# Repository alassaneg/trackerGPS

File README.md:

# trackerGPS
Tracker GPS with gsm functionality and eSim.
Kicad files in the folder "/trackerGPS"

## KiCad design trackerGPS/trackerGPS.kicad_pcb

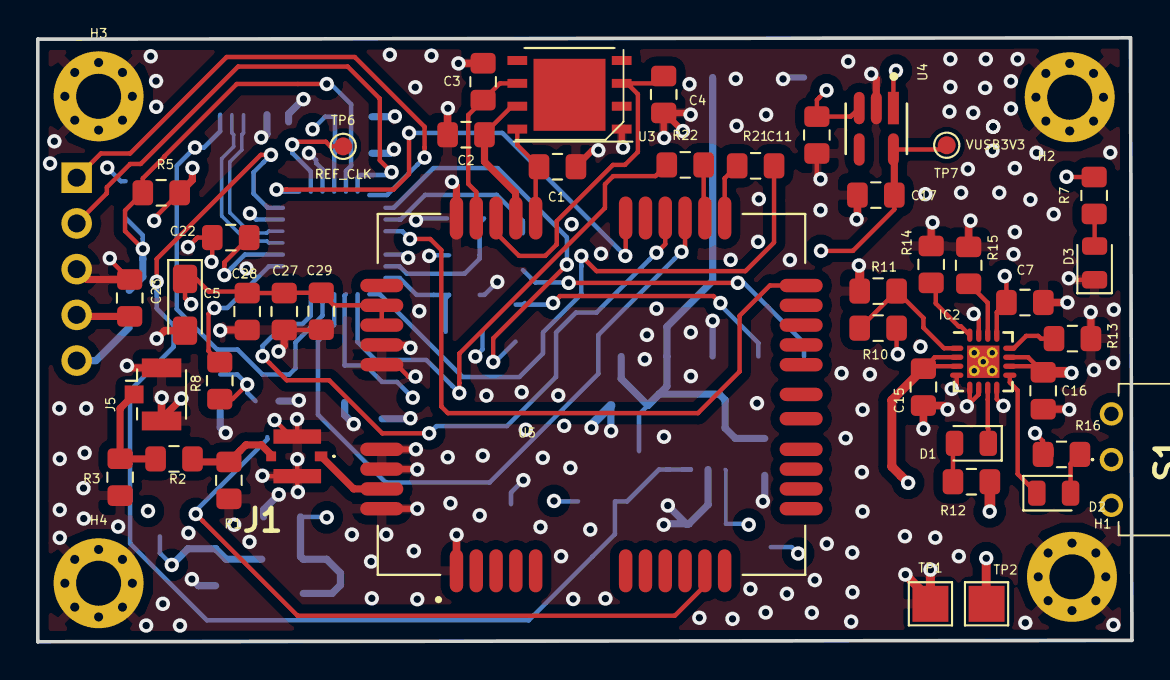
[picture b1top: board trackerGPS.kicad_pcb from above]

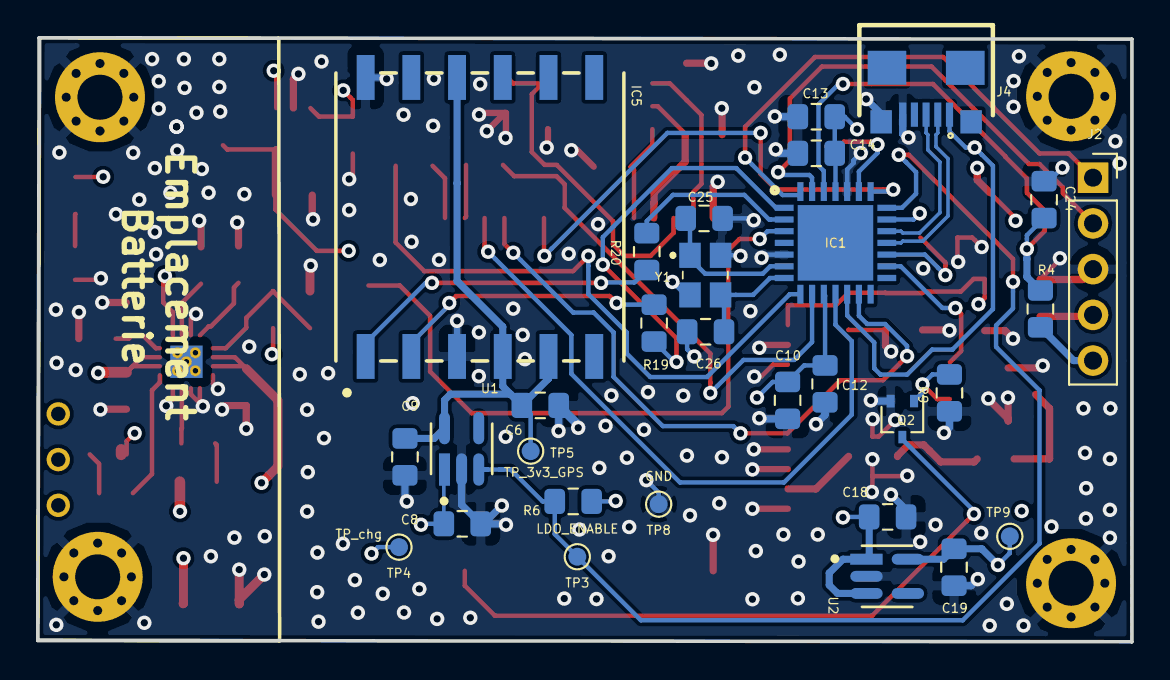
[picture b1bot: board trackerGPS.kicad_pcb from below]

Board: 4 copper layers, 60.8 x 33.6 mm, 78 parts (30 on the bottom side), 50 nets.

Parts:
C1, C7: 1uF; C_0805_2012Metric_Pad1.15x1.40mm_HandSolder
C2, C3, C4, C27: 33pF; C_0805_2012Metric_Pad1.15x1.40mm_HandSolder
C5: 100uF; CP_EIA-3216-10_Kemet-I_Pad1.58x1.35mm_HandSolder
C6, C22: 10uF; C_0805_2012Metric_Pad1.15x1.40mm_HandSolder
C8, C9, C15, C16, C18, C19: 4.7uF; C_0805_2012Metric_Pad1.15x1.40mm_HandSolder
C10, C11, C13, C17, C23, C24, C28: 100nF; C_0805_2012Metric_Pad1.15x1.40mm_HandSolder
C12, C14: 1nF; C_0805_2012Metric_Pad1.15x1.40mm_HandSolder
C25, C26: 28pF; C_0805_2012Metric_Pad1.15x1.40mm_HandSolder
C29: 10pF; C_0805_2012Metric_Pad1.15x1.40mm_HandSolder
D1, D2, D3: LED_Small; LED_0805_2012Metric
H1, H2, H3, H4: MountingHole_Pad; MountingHole_2.5mm_Pad_Via
IC1: PIC32MM0256GPM028-I_ML; QFN65P600X600X100-29N-D
IC2: BQ24072TRGTT; QFN-16-1EP_3x3mm_P0.5mm_EP2.7x2.7mm_ThermalVias
IC5: L86-M33; L80-M39
J1: MS-156HF; MS156HF
J2: Conn; PinSocket_1x05_P2.54mm_Vertical
J4: USB_B_Micro; DX4R005HJ5
J5: Conn_Coaxial; U.FL_Hirose_U.FL-R-SMT-1_Vertical
Q2: BC847BW,115; SOT-323_SC-70
R1, R3: R_Small; R_0805_2012Metric_Pad1.15x1.40mm_HandSolder
R2, R6, R15, R19, R20, R21, R22: 0ohm; R_0805_2012Metric_Pad1.15x1.40mm_HandSolder
R4: 602ohm; R_0805_2012Metric_Pad1.15x1.40mm_HandSolder
R5, R8: 10kOhm; R_0805_2012Metric_Pad1.15x1.40mm_HandSolder
R7: 1.9kOhm; R_0805_2012Metric_Pad1.15x1.40mm_HandSolder
R9: 47kOhm; R_0805_2012Metric_Pad1.15x1.40mm_HandSolder
R10: 200kOhm; R_0805_2012Metric_Pad1.15x1.40mm_HandSolder
R11: 49.9kOhm; R_0805_2012Metric_Pad1.15x1.40mm_HandSolder
R12, R16: 1.5kOhm; R_0805_2012Metric_Pad1.15x1.40mm_HandSolder
R13: NP; R_0805_2012Metric_Pad1.15x1.40mm_HandSolder
R14: 909 ohm; R_0805_2012Metric_Pad1.15x1.40mm_HandSolder
S1: 450302014072
TP1: Battery_GND; TestPoint_Pad_2.0x2.0mm
TP2: Battery+; TestPoint_Pad_2.0x2.0mm
TP3: LDO_ENABLE; TestPoint_Pad_D1.0mm
TP4: TP_chg; TestPoint_Pad_D1.0mm
TP5: TP_3v3_GPS; TestPoint_Pad_D1.0mm
TP6: REF_CLK; TestPoint_Pad_D1.0mm
TP7: VUSB3V3; TestPoint_Pad_D1.0mm
TP8: GND; TestPoint_Pad_D1.0mm
TP9: TP_3v3_UC; TestPoint_Pad_D1.0mm
U1, U2, U4: REG113NA-3.3_3K; Texas_Instruments-DBV0005A-0-0-IPC_A
U3: MFF2_E_SIM; DFN-8-1EP_6x5mm_P1.27mm_EP4x4mm
U5: M95; XCVR_M95
Y1: ABM8G-48.000MHZ-18-D2Y-T; ABM8G48000MHZ18D2YT

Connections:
/gpsModule/UART_RX_GSM: IC5.1, R20.2
/gpsModule/UART_TX_GSM: IC5.2, R19.1
/microcontroller/CALL_RECEIVED: IC1.22, U5.26
/microcontroller/LDO_ENABLE: IC1.21, R6.1, TP3.1, U1.3
/microcontroller/SLEEP: IC1.3, U5.20
/microcontroller/UART_CTS3_UC: IC1.11, U5.23
/microcontroller/UART_RX2_UC: IC1.1, R19.2
/microcontroller/UART_RX3_UC: IC1.9, R22.1
/microcontroller/UART_TX2_UC: IC1.2, R20.1
/microcontroller/UART_TX3_UC: IC1.8, R21.2
/microcontroller/USB+: IC1.19, J4.3
/microcontroller/USB-: IC1.18, J4.2
/microcontroller/VBUS: C7.1, C11.1, IC1.12, IC2.13, J4.1, R10.2, U4.1, U4.3
/microcontroller/VUSB3V3: C17.1, IC1.20, TP7.1, U4.5
/powerSupply/Vcc_3.3V_GPS: C6.1, C9.1, IC5.4, IC5.5, IC5.10, TP5.1, U1.5
/powerSupply/Vcc_3.3V_UC: C10.1, C12.1, C13.1, C14.1, C19.1, C23.1, IC1.10, IC1.25, J2.4, R5.2, TP9.1, U2.5
/powerSupply/Vcc_BAT_GSM: C5.1, C8.1, C16.1, C18.1, C27.1, C28.1, C29.1, IC2.10, IC2.11, R6.2, R7.2, R12.2, R16.2, TP4.1, U1.1, U2.1, U2.3, U5.33, U5.34
/simModule/GSM_POWER_ON: Q2.3, U5.10
/simModule/UART_GSM_RTS: IC1.13, U5.24
/simModule/UART_RX_GSM: R21.1, U5.21
/simModule/UART_TX_GSM: R22.2, U5.22
GND: C1.2, C2.2, C3.2, C4.2, C5.2, C6.2, C7.2, C8.2, C9.2, C10.2, C11.2, C12.2, C13.2, C14.2, C15.2, C16.2, C17.2, C18.2, C19.2, C22.2, C23.2, C24.2, C25.2, C26.2, C27.2, C28.2, C29.2, D3.1, H1.1, H2.1, H3.1, H4.1, IC1.5, IC1.24, IC2.4, IC2.5, IC2.6, IC2.8, IC2.15, IC2.17, IC5.3, IC5.12, J1.MP1, J1.MP2, J2.3, J4.5, J4.6, J5.2, Q2.2, R1.1, R3.2, R9.2, R11.1, R13.1, R14.1, R15.1, TP1.1, TP8.1, U1.2, U2.2, U3.1, U4.2, U5.1, U5.31, U5.35, U5.36, U5.37, U5.38, U5.40, Y1.2, Y1.4
unnamed: C1.1, U3.8, U5.27
unnamed: C2.1, U3.7, U5.28
unnamed: C3.1, U3.6, U5.30
unnamed: C4.1, U3.3, U5.29
unnamed: C15.1, IC2.2, IC2.3, S1.2
unnamed: C22.1, IC1.17
unnamed: C24.1, IC1.26, R4.1, R5.1
unnamed: C25.1, IC1.6, Y1.1
unnamed: C26.1, IC1.7, Y1.3
unnamed: D1.1, IC2.7
unnamed: D1.2, R12.1
unnamed: D2.1, IC2.9
unnamed: D2.2, R16.1
unnamed: D3.2, R7.1
unnamed: IC1.16, R8.2
unnamed: IC1.23, TP6.1
unnamed: IC1.27, J2.2
unnamed: IC1.28, J2.1
unnamed: IC2.1, R10.1, R11.2
unnamed: IC2.12, R13.2
unnamed: IC2.14, R15.2
unnamed: IC2.16, R14.2
unnamed: J1.A1, U5.39
unnamed: J1.C1, R1.2, R2.1
unnamed: J2.5, R4.2
unnamed: J5.1, R2.2, R3.1
unnamed: Q2.1, R8.1, R9.1
unnamed: S1.1, TP2.1

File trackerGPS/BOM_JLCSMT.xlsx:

Comment | Designator | Footprint | LCSC Part #（optional）
1uF | C1, C7 | 0805_C | C28323
33pF | C2 , C3, C4, C27 | 0805_C | C1814
100uF | C5 | CP_EIA-3216-10_Kemet-I_Pad1.58x1.35mm_HandSolder | C313517
10uF | C6, C22 | 0805_C | C282736
4.7uF | C8, C9, C15, C16, C18, C19 | 0805_C | C354262
1nF | C12, C14 | 0805_C | C501242
28pF | C25, C26 | 0805_C
100nF | C10, C11, C13, C17, C23, C24, C28 | 0805_C | C167411
10pF | C29 | 0805_C | C157608
LED_Small | D1, D2, D3 | 0805_L | C188728
PIC32MM0256GPM028-I_ML | IC1 | QFN65P600X600X100-29N-D
BQ24072TRGTT | IC2 | QFN-16-1EP_3x3mm_P0.5mm_EP2.7x2.7mm_ThermalVias
L86-M33 | IC5 | L86-M33
Conn | J2 | PinSocket_1x05_P2.54mm_Vertical
902-9235 | J3 | 902-9235
USB_B_Micro | J4 | DX4R005HJ5
Conn_Coaxial | J1 | U.FL_Hirose_U.FL-R-SMT-1_Vertical
BC847BW,115 | Q2 | SOT-323_SC-70 | C8659
R_Small | R1 | 0805_R
R_Small | R3 | 0805_R
602ohm | R4 | 0805_R | C17777
10kOhm | R5, R8 | 0805_R | C17414
1.9kOhm | R7 | 0805_R
47kOhm | R9 | 0805_R | C17713
200kOhm | R10 | 0805_R | C17539
49.9kOhm | R11 | 0805_R | C63044
NP | R13 | 0805_R
909 ohm | R14 | 0805_R | C17863
1.5kOhm | R12, R16 | 0805_R | C4310
0ohm | R2, R6, R15, R19, R20, R21, R22 | 0805_R | C17477
REG113NA-3.3_3K | U1, U2, U4 | REG113NA
MFF2_E_SIM | U3 | Package_DFN_QFN:DFN-8-1EP_6x5mm_P1.27mm_EP4x4mm
M95 | U5 | Quectel_M95
ABM8G-48.000MHZ-18-D2Y-T | Y1 | ABM8G-12.288MHZ-18-D2Y-T

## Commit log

2021-03-29 new file: "Bilan energ\303\251tique tracker GPS.xlsx" new file: Datasheet/001-91445_AN91445_Antenna_Design_and_RF_Layout_Guidelines(1).pdf new file: Datasheet/GPS module SE868 V3/1VV0301162_V13_Softw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
2021-03-31 modified: trackerGPS/microcontroller.bak modified: trackerGPS/powerSupply.bak modified: trackerGPS/powerSupply.sch modified: trackerGPS/trackerGPS-cache.lib modified: trackerGPS/trackerGPS.bak modifi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
2021-04-01 added battery charger BQ24072T modified: trackerGPS/powerSupply.bak modified: trackerGPS/powerSupply.sch modified: trackerGPS/sym-lib-table modified: trackerGPS/trackerGPS-cache.lib new file: tracker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
2021-04-03 Component placed
2021-04-03 Component placed modified: trackerGPS/microcontroller.bak modified: trackerGPS/microcontroller.sch modified: trackerGPS/powerSupply.bak modified: trackerGPS/powerSupply.sch modified: trackerGPS/simMo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
2021-04-06 PCB completed with test points modified: trackerGPS/gpsModule.bak modified: trackerGPS/gpsModule.sch modified: trackerGPS/microcontroller.bak modified: trackerGPS/microcontroller.sch modified: tracke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
2021-04-06 Datasheets updated
2021-04-06 Replaced TLV75201 by REG113NA modified: "Bilan energ\303\251tique tracker GPS.xlsx" modified: trackerGPS/microcontroller.bak modified: trackerGPS/powerSupply.bak modified: trackerGPS/powerSupply.sch 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
2021-04-21 added BOM and first prototype ready
